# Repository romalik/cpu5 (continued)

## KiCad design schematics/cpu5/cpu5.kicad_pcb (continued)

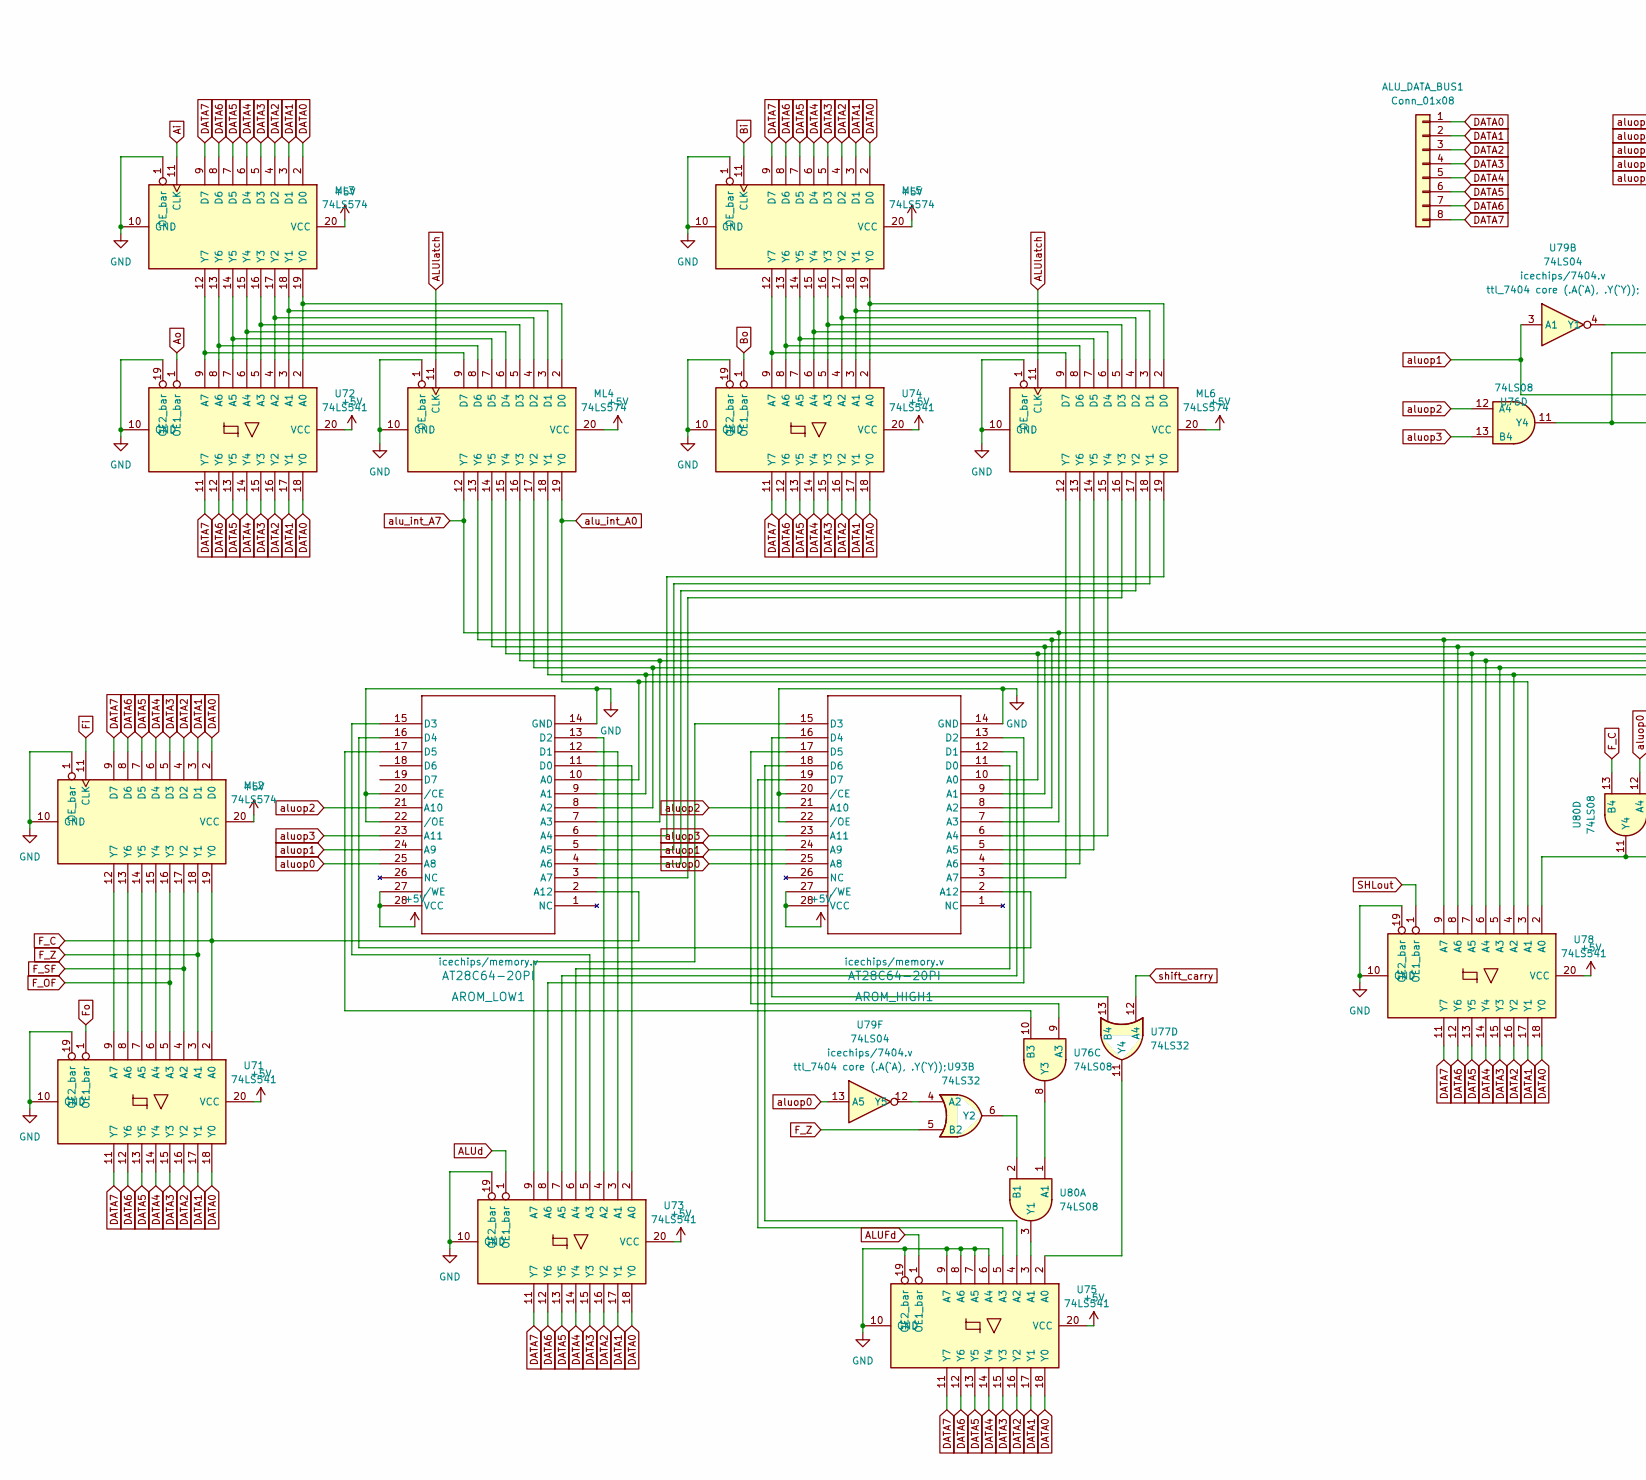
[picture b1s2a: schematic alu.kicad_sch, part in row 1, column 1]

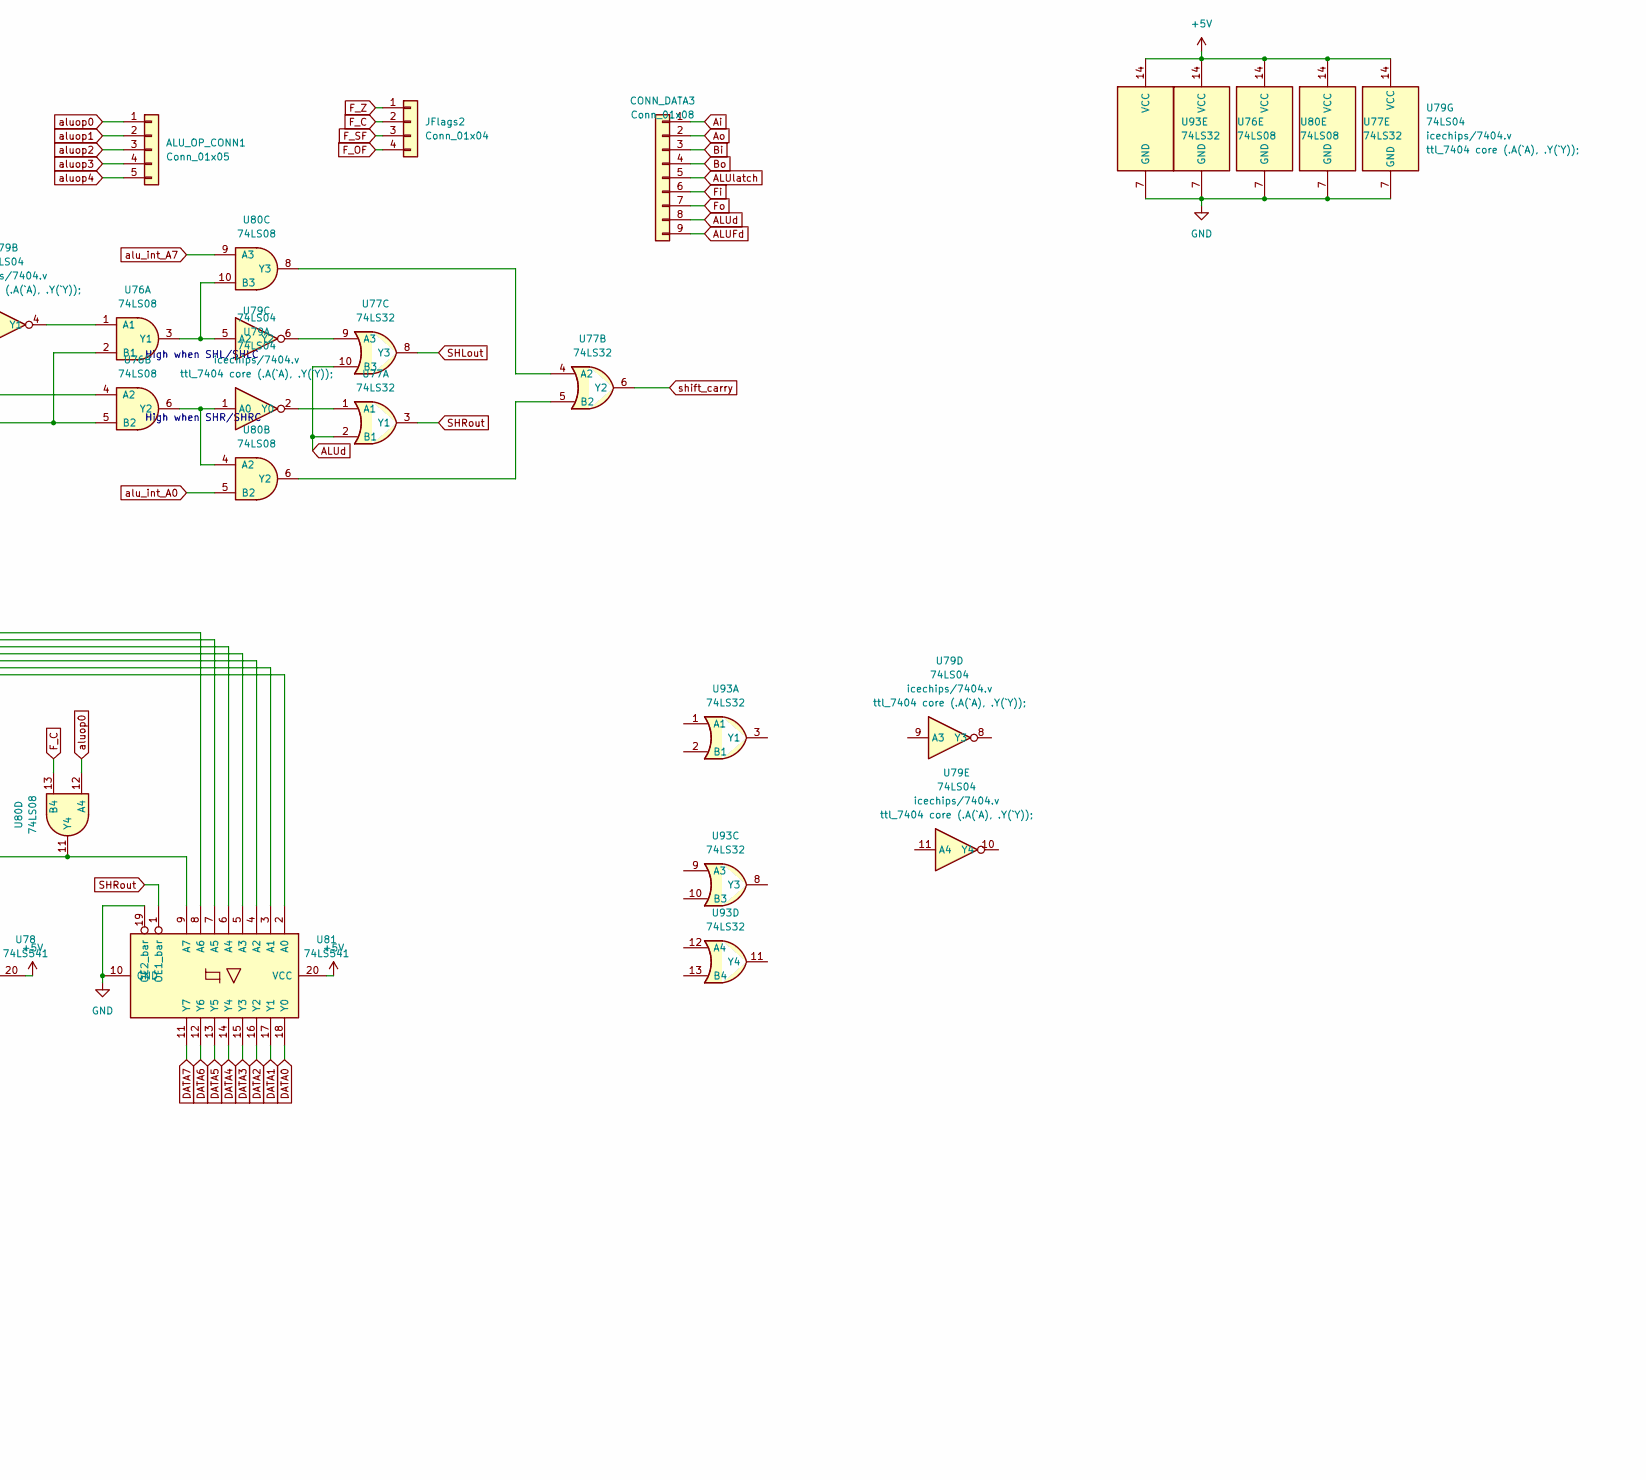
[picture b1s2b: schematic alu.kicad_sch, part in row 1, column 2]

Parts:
ALU_DATA_BUS1: Conn_01x08; PinHeader_1x08_P2.54mm_Vertical
ALU_OP_CONN1: Conn_01x05; PinHeader_1x05_P2.54mm_Vertical
AROM_HIGH1: AT28C64-20PI; DIP-28_W15.24mm
AROM_LOW1: AT28C64-20PI; DIP-28_W15.24mm
CONN_DATA3: Conn_01x08; PinHeader_1x09_P2.54mm_Vertical
JFlags2: Conn_01x04; PinHeader_1x04_P1.00mm_Vertical
ML2, ML3, ML4, ML5, ML6: 74LS574; DIP-20_W7.62mm
U71, U72, U73, U74, U75, U78, U81: 74LS541; DIP-20_W7.62mm
U76, U80: 74LS08; DIP-14_W7.62mm
U77, U93: 74LS32; DIP-14_W7.62mm
U79: 74LS04; DIP-14_W7.62mm

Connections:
+5V: AROM_HIGH1.27 (/WE), AROM_HIGH1.28 (VCC), AROM_LOW1.27 (/WE), AROM_LOW1.28 (VCC), ML2.20 (VCC), ML3.20 (VCC), ML4.20 (VCC), ML5.20 (VCC), ML6.20 (VCC), U71.20 (VCC), U72.20 (VCC), U73.20 (VCC), U74.20 (VCC), U75.20 (VCC), U76.14 (VCC), U77.14 (VCC), U78.20 (VCC), U79.14 (VCC), U80.14 (VCC), U81.20 (VCC), U93.14 (VCC); also elsewhere on the board
ALUFd: CONN_DATA3.9, U75.1 (OE1_bar); also elsewhere on the board
ALUd: CONN_DATA3.8, U73.1 (OE1_bar), U77.2 (B1), U77.10 (B3); also elsewhere on the board
ALUlatch: CONN_DATA3.5, ML4.11 (CLK), ML6.11 (CLK); also elsewhere on the board
Ai: CONN_DATA3.1, ML3.11 (CLK); also elsewhere on the board
Ao: CONN_DATA3.2, U72.1 (OE1_bar); also elsewhere on the board
Bi: CONN_DATA3.3, ML5.11 (CLK); also elsewhere on the board
Bo: CONN_DATA3.4, U74.1 (OE1_bar); also elsewhere on the board
DATA0: ALU_DATA_BUS1.1, ML2.2 (D0), ML3.2 (D0), ML5.2 (D0), U71.18 (Y0), U72.18 (Y0), U73.18 (Y0), U74.18 (Y0), U75.18 (Y0), U78.18 (Y0), U81.18 (Y0); also elsewhere on the board
DATA1: ALU_DATA_BUS1.2, ML2.3 (D1), ML3.3 (D1), ML5.3 (D1), U71.17 (Y1), U72.17 (Y1), U73.17 (Y1), U74.17 (Y1), U75.17 (Y1), U78.17 (Y1), U81.17 (Y1); also elsewhere on the board
DATA2: ALU_DATA_BUS1.3, ML2.4 (D2), ML3.4 (D2), ML5.4 (D2), U71.16 (Y2), U72.16 (Y2), U73.16 (Y2), U74.16 (Y2), U75.16 (Y2), U78.16 (Y2), U81.16 (Y2); also elsewhere on the board
DATA3: ALU_DATA_BUS1.4, ML2.5 (D3), ML3.5 (D3), ML5.5 (D3), U71.15 (Y3), U72.15 (Y3), U73.15 (Y3), U74.15 (Y3), U75.15 (Y3), U78.15 (Y3), U81.15 (Y3); also elsewhere on the board
DATA4: ALU_DATA_BUS1.5, ML2.6 (D4), ML3.6 (D4), ML5.6 (D4), U71.14 (Y4), U72.14 (Y4), U73.14 (Y4), U74.14 (Y4), U75.14 (Y4), U78.14 (Y4), U81.14 (Y4); also elsewhere on the board
DATA5: ALU_DATA_BUS1.6, ML2.7 (D5), ML3.7 (D5), ML5.7 (D5), U71.13 (Y5), U72.13 (Y5), U73.13 (Y5), U74.13 (Y5), U75.13 (Y5), U78.13 (Y5), U81.13 (Y5); also elsewhere on the board
DATA6: ALU_DATA_BUS1.7, ML2.8 (D6), ML3.8 (D6), ML5.8 (D6), U71.12 (Y6), U72.12 (Y6), U73.12 (Y6), U74.12 (Y6), U75.12 (Y6), U78.12 (Y6), U81.12 (Y6); also elsewhere on the board
DATA7: ALU_DATA_BUS1.8, ML2.9 (D7), ML3.9 (D7), ML5.9 (D7), U71.11 (Y7), U72.11 (Y7), U73.11 (Y7), U74.11 (Y7), U75.11 (Y7), U78.11 (Y7), U81.11 (Y7); also elsewhere on the board
F_C: AROM_LOW1.2 (A12), JFlags2.2, ML2.19 (Y0), U71.2 (A0), U80.13 (B4); also elsewhere on the board
F_OF: JFlags2.4, ML2.16 (Y3), U71.5 (A3); also elsewhere on the board
F_SF: JFlags2.3, ML2.17 (Y2), U71.4 (A2); also elsewhere on the board
F_Z: JFlags2.1, ML2.18 (Y1), U71.3 (A1), U93.5 (B2); also elsewhere on the board
Fi: CONN_DATA3.6, ML2.11 (CLK); also elsewhere on the board
Fo: CONN_DATA3.7, U71.1 (OE1_bar); also elsewhere on the board
GND: AROM_HIGH1.14 (GND), AROM_HIGH1.20 (/CE), AROM_HIGH1.22 (/OE), AROM_LOW1.14 (GND), AROM_LOW1.20 (/CE), AROM_LOW1.22 (/OE), ML2.1 (OE_bar), ML2.10 (GND), ML3.1 (OE_bar), ML3.10 (GND), ML4.1 (OE_bar), ML4.10 (GND), ML5.1 (OE_bar), ML5.10 (GND), ML6.1 (OE_bar), ML6.10 (GND), U71.10 (GND), U71.19 (OE2_bar), U72.10 (GND), U72.19 (OE2_bar), U73.10 (GND), U73.19 (OE2_bar), U74.10 (GND), U74.19 (OE2_bar), U75.6 (A4), U75.7 (A5), U75.8 (A6), U75.9 (A7), U75.10 (GND), U75.19 (OE2_bar), U76.7 (GND), U77.7 (GND), U78.10 (GND), U78.19 (OE2_bar), U79.7 (GND), U80.7 (GND), U81.10 (GND), U81.19 (OE2_bar), U93.7 (GND); also elsewhere on the board
IR0: ALU_OP_CONN1.1, AROM_HIGH1.25 (A8), AROM_LOW1.25 (A8), U79.13 (A5), U80.12 (A4); also elsewhere on the board
IR1: ALU_OP_CONN1.2, AROM_HIGH1.24 (A9), AROM_LOW1.24 (A9), U76.4 (A2), U79.3 (A1); also elsewhere on the board
IR2: ALU_OP_CONN1.3, AROM_HIGH1.21 (A10), AROM_LOW1.21 (A10), U76.12 (A4); also elsewhere on the board
IR3: ALU_OP_CONN1.4, AROM_HIGH1.23 (A11), AROM_LOW1.23 (A11), U76.13 (B4); also elsewhere on the board
IR4: ALU_OP_CONN1.5; also elsewhere on the board
unnamed: AROM_HIGH1.2 (A12), AROM_LOW1.16 (D4)
unnamed: AROM_HIGH1.3 (A7), ML6.12 (Y7)
unnamed: AROM_HIGH1.4 (A6), ML6.13 (Y6)
unnamed: AROM_HIGH1.5 (A5), ML6.14 (Y5)
unnamed: AROM_HIGH1.6 (A4), ML6.15 (Y4)
unnamed: AROM_HIGH1.8 (A2), ML4.13 (Y6), U78.9 (A7), U81.7 (A5)
unnamed: AROM_HIGH1.9 (A1), ML4.14 (Y5), U78.8 (A6), U81.6 (A4)
unnamed: AROM_HIGH1.10 (A0), ML4.15 (Y4), U78.7 (A5), U81.5 (A3)
unnamed: AROM_HIGH1.11 (D0), U73.6 (A4)
unnamed: AROM_HIGH1.12 (D1), U73.7 (A5)
unnamed: AROM_HIGH1.13 (D2), U73.8 (A6)
unnamed: AROM_HIGH1.15 (D3), U73.9 (A7)
unnamed: AROM_HIGH1.16 (D4), U77.13 (B4)
unnamed: AROM_HIGH1.17 (D5), U76.9 (A3)
unnamed: AROM_HIGH1.18 (D6), U75.4 (A2)
unnamed: AROM_HIGH1.19 (D7), U75.5 (A3)
unnamed: AROM_LOW1.3 (A7), ML6.16 (Y3)
unnamed: AROM_LOW1.4 (A6), ML6.17 (Y2)
unnamed: AROM_LOW1.5 (A5), ML6.18 (Y1)
unnamed: AROM_LOW1.6 (A4), ML6.19 (Y0)
unnamed: AROM_LOW1.7 (A3), ML4.16 (Y3), U78.6 (A4), U81.4 (A2)
unnamed: AROM_LOW1.8 (A2), ML4.17 (Y2), U78.5 (A3), U81.3 (A1)
unnamed: AROM_LOW1.9 (A1), ML4.18 (Y1), U78.4 (A2), U81.2 (A0)
unnamed: AROM_LOW1.11 (D0), U73.2 (A0)
unnamed: AROM_LOW1.12 (D1), U73.3 (A1)
unnamed: AROM_LOW1.13 (D2), U73.4 (A2)
unnamed: AROM_LOW1.15 (D3), U73.5 (A3)
unnamed: AROM_LOW1.17 (D5), U76.10 (B3)
unnamed: ML2.12 (Y7), U71.9 (A7)
unnamed: ML2.13 (Y6), U71.8 (A6)
unnamed: ML2.14 (Y5), U71.7 (A5)
unnamed: ML2.15 (Y4), U71.6 (A4)
unnamed: ML3.12 (Y7), ML4.9 (D7), U72.9 (A7)
unnamed: ML3.13 (Y6), ML4.8 (D6), U72.8 (A6)
unnamed: ML3.14 (Y5), ML4.7 (D5), U72.7 (A5)
unnamed: ML3.15 (Y4), ML4.6 (D4), U72.6 (A4)
unnamed: ML3.16 (Y3), ML4.5 (D3), U72.5 (A3)
unnamed: ML3.17 (Y2), ML4.4 (D2), U72.4 (A2)
unnamed: ML3.18 (Y1), ML4.3 (D1), U72.3 (A1)
unnamed: ML3.19 (Y0), ML4.2 (D0), U72.2 (A0)
unnamed: ML5.12 (Y7), ML6.9 (D7), U74.9 (A7)
unnamed: ML5.13 (Y6), ML6.8 (D6), U74.8 (A6)
unnamed: ML5.14 (Y5), ML6.7 (D5), U74.7 (A5)
unnamed: ML5.15 (Y4), ML6.6 (D4), U74.6 (A4)
unnamed: ML5.16 (Y3), ML6.5 (D3), U74.5 (A3)
unnamed: ML5.17 (Y2), ML6.4 (D2), U74.4 (A2)
unnamed: ML5.18 (Y1), ML6.3 (D1), U74.3 (A1)
unnamed: ML5.19 (Y0), ML6.2 (D0), U74.2 (A0)
unnamed: U75.2 (A0), U77.11 (Y4)
unnamed: U75.3 (A1), U80.3 (Y1)
unnamed: U76.1 (A1), U79.4 (Y1)
unnamed: U76.3 (Y1), U79.5 (A2), U80.10 (B3)
unnamed: U76.6 (Y2), U79.1 (A0), U80.4 (A2)
unnamed: U76.8 (Y3), U80.1 (A1)
unnamed: U76.2 (B1), U76.5 (B2), U76.11 (Y4)
unnamed: U77.1 (A1), U79.2 (Y0)
unnamed: U77.4 (A2), U80.8 (Y3)
unnamed: U77.5 (B2), U80.6 (Y2)
unnamed: U77.9 (A3), U79.6 (Y2)
unnamed: U78.2 (A0), U80.11 (Y4), U81.9 (A7)
unnamed: U79.12 (Y5), U93.4 (A2)
unnamed: U80.2 (B1), U93.6 (Y2)
SHLout: U77.8 (Y3), U78.1 (OE1_bar)
SHRout: U77.3 (Y1), U81.1 (OE1_bar)
alu_int_A0: AROM_LOW1.10 (A0), ML4.19 (Y0), U78.3 (A1), U80.5 (B2)
alu_int_A7: AROM_HIGH1.7 (A3), ML4.12 (Y7), U80.9 (A3), U81.8 (A6)
shift_carry: U77.6 (Y2), U77.12 (A4)

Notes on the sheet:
High when SHR/SHRC
High when SHL/SHLC

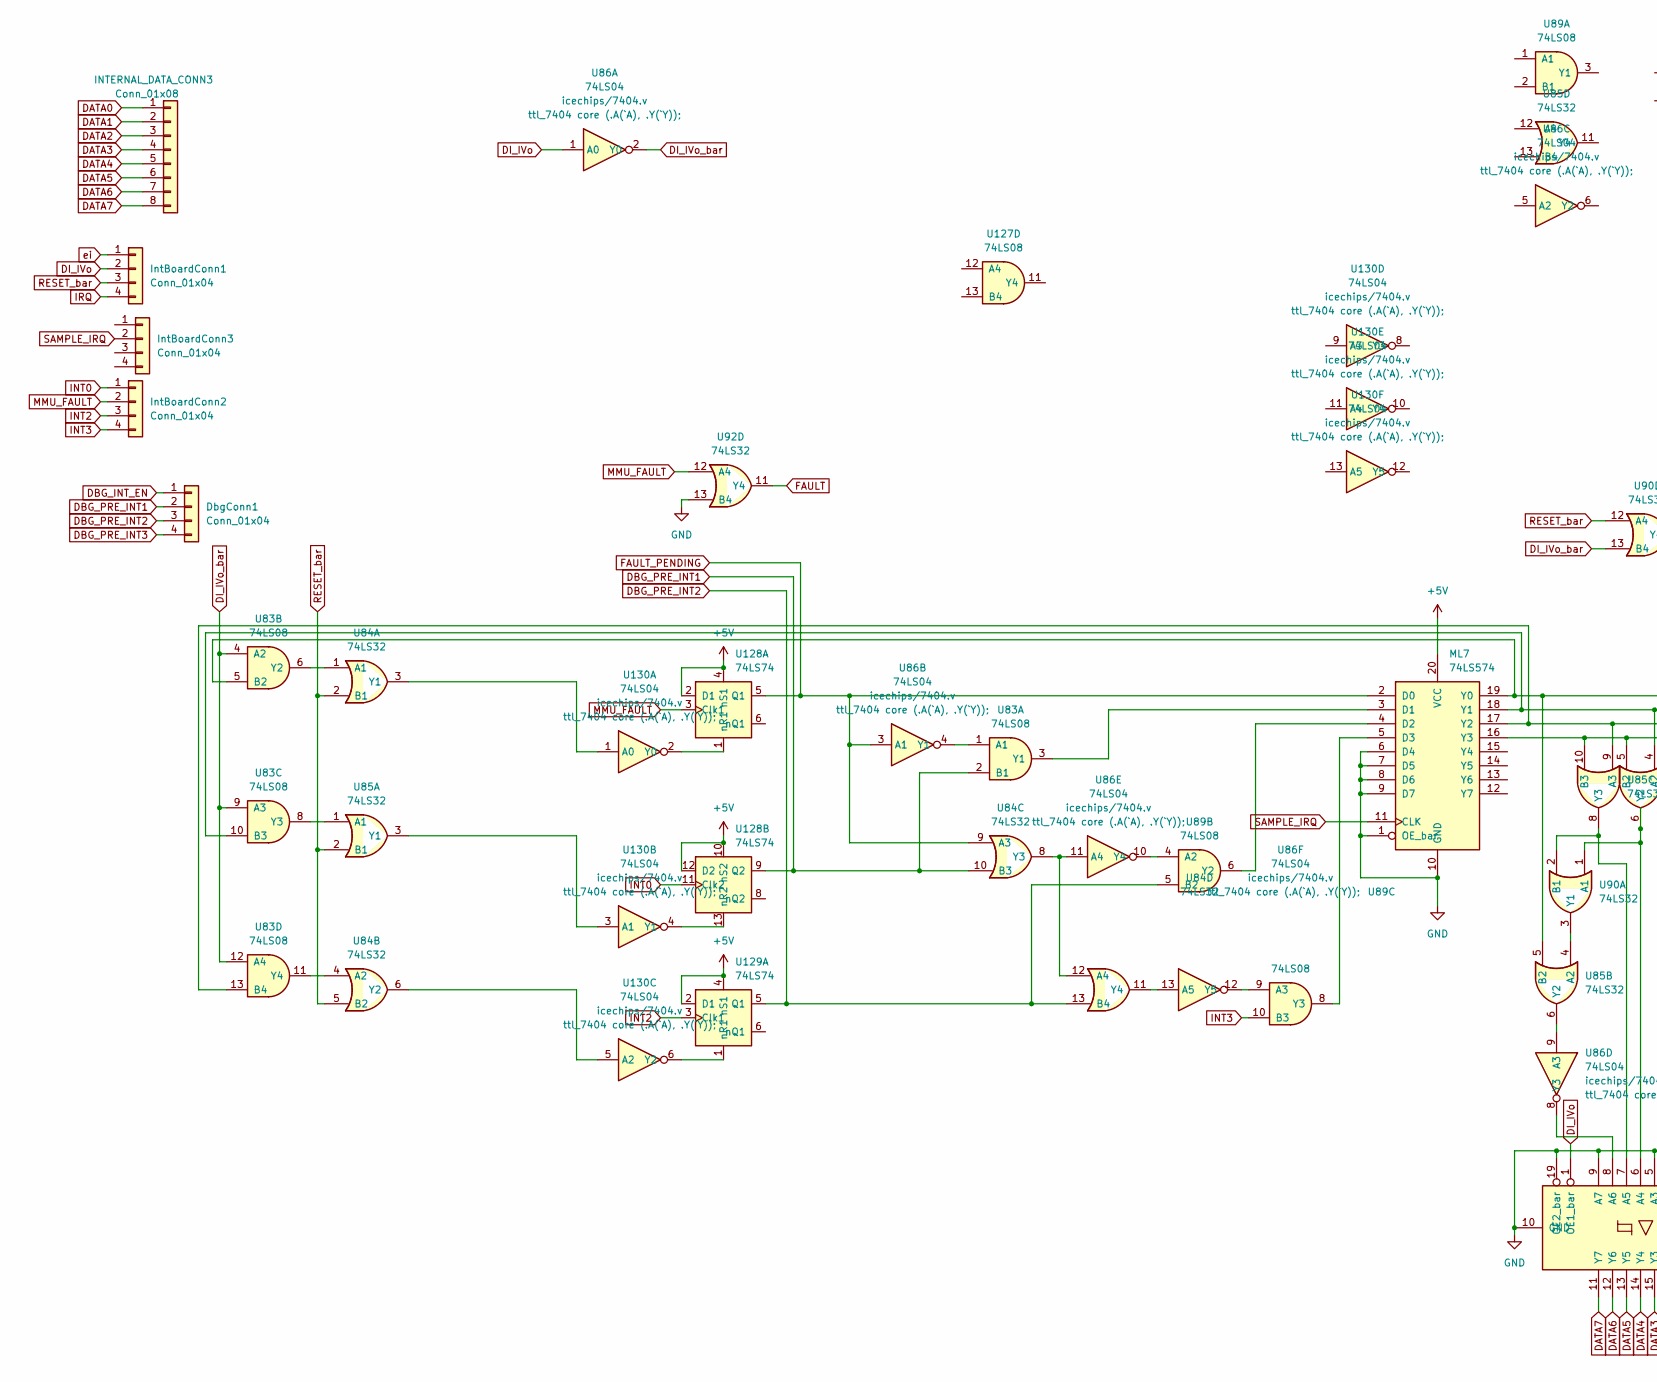
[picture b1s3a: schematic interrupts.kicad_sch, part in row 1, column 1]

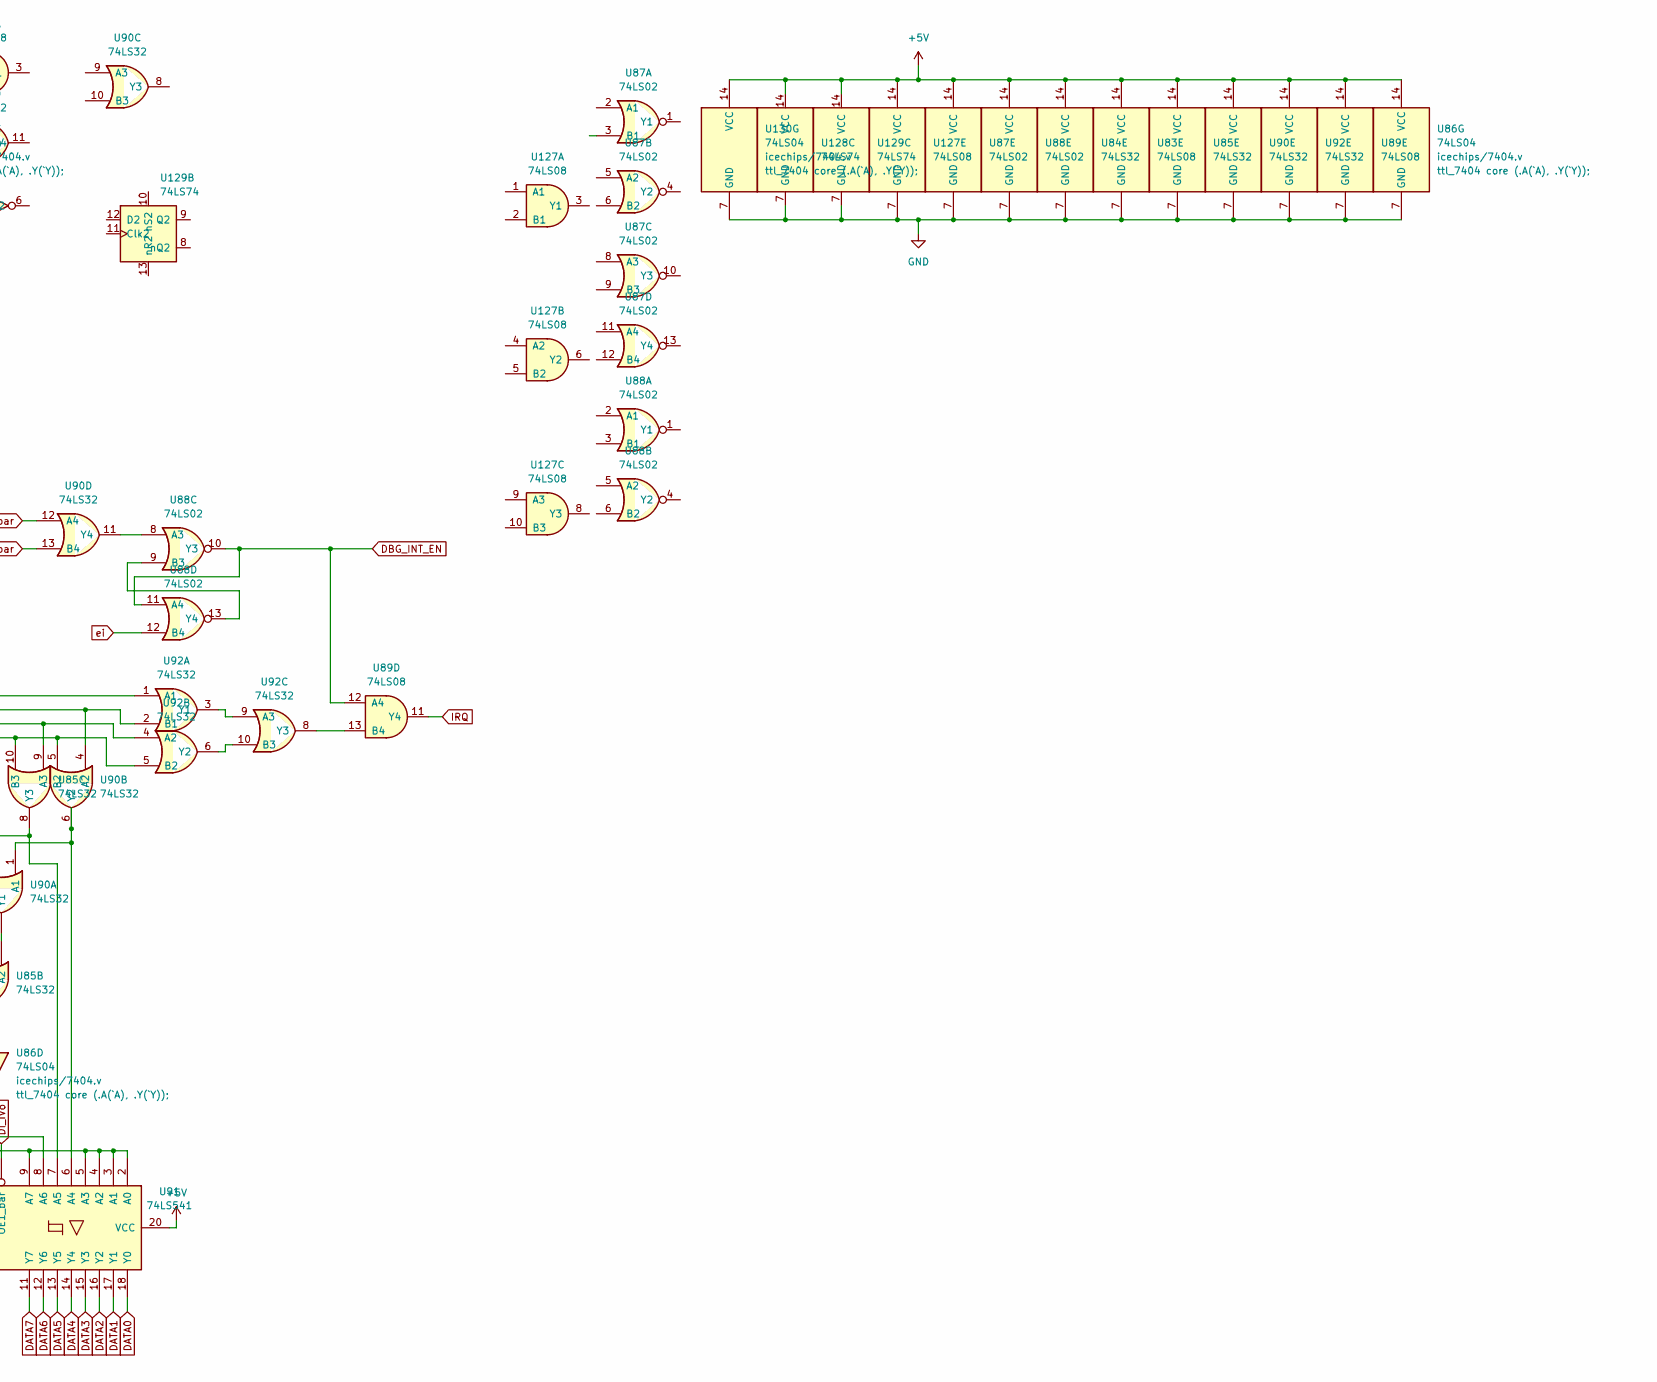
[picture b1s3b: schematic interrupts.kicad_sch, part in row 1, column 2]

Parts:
DbgConn1: Conn_01x04; PinHeader_1x04_P1.00mm_Vertical
INTERNAL_DATA_CONN3: Conn_01x08; PinHeader_1x08_P2.54mm_Vertical
IntBoardConn1, IntBoardConn2, IntBoardConn3: Conn_01x04; PinHeader_1x04_P1.00mm_Vertical
ML7: 74LS574; DIP-20_W7.62mm
U83, U89, U127: 74LS08; DIP-14_W7.62mm
U84, U85, U90, U92: 74LS32; DIP-14_W7.62mm
U86, U130: 74LS04; DIP-14_W7.62mm
U87, U88: 74LS02; DIP-14_W7.62mm
U91: 74LS541; DIP-20_W7.62mm
U128, U129: 74LS74; DIP-14_W7.62mm

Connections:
+5V: ML7.20 (VCC), U83.14 (VCC), U84.14 (VCC), U85.14 (VCC), U86.14 (VCC), U87.14 (VCC), U88.14 (VCC), U89.14 (VCC), U90.14 (VCC), U91.20 (VCC), U92.14 (VCC), U127.14 (VCC), U128.2 (D1), U128.4 (nS1), U128.10 (nS2), U128.12 (D2), U128.14 (VCC), U129.2 (D1), U129.4 (nS1), U129.14 (VCC), U130.14 (VCC); also elsewhere on the board
DATA0: INTERNAL_DATA_CONN3.1, U91.18 (Y0); also elsewhere on the board
DATA1: INTERNAL_DATA_CONN3.2, U91.17 (Y1); also elsewhere on the board
DATA2: INTERNAL_DATA_CONN3.3, U91.16 (Y2); also elsewhere on the board
DATA3: INTERNAL_DATA_CONN3.4, U91.15 (Y3); also elsewhere on the board
DATA4: INTERNAL_DATA_CONN3.5, U91.14 (Y4); also elsewhere on the board
DATA5: INTERNAL_DATA_CONN3.6, U91.13 (Y5); also elsewhere on the board
DATA6: INTERNAL_DATA_CONN3.7, U91.12 (Y6); also elsewhere on the board
DATA7: INTERNAL_DATA_CONN3.8, U91.11 (Y7); also elsewhere on the board
DBG_INT_EN: DbgConn1.1, U88.10 (Y3), U88.11 (A4), U89.12 (A4); also elsewhere on the board
DBG_PRE_INT1: DbgConn1.2, U83.2 (B1), U84.10 (B3), U128.9 (Q2); also elsewhere on the board
DBG_PRE_INT2: DbgConn1.3, U84.13 (B4), U89.5 (B2), U129.5 (Q1); also elsewhere on the board
DBG_PRE_INT3: DbgConn1.4; also elsewhere on the board
DI_IVo: IntBoardConn1.2, U86.1 (A0), U91.1 (OE1_bar); also elsewhere on the board
DI_IVo_bar: U83.4 (A2), U83.9 (A3), U83.12 (A4), U86.2 (Y0), U90.13 (B4)
FAULT: U92.11 (Y4); also elsewhere on the board
FAULT_PENDING: ML7.2 (D0), U84.9 (A3), U86.3 (A1), U128.5 (Q1); also elsewhere on the board
GND: ML7.1 (OE_bar), ML7.6 (D4), ML7.7 (D5), ML7.8 (D6), ML7.9 (D7), ML7.10 (GND), U83.7 (GND), U84.7 (GND), U85.7 (GND), U86.7 (GND), U87.7 (GND), U88.7 (GND), U89.7 (GND), U90.7 (GND), U91.2 (A0), U91.3 (A1), U91.4 (A2), U91.5 (A3), U91.9 (A7), U91.10 (GND), U91.19 (OE2_bar), U92.7 (GND), U92.13 (B4), U127.7 (GND), U128.7 (GND), U129.7 (GND), U130.7 (GND); also elsewhere on the board
INT0: IntBoardConn2.1, U128.11 (Clk2)
INT2: IntBoardConn2.3, U129.3 (Clk1)
INT3: IntBoardConn2.4, U89.10 (B3)
IRQ: IntBoardConn1.4, U89.11 (Y4); also elsewhere on the board
MMU_FAULT: IntBoardConn2.2, U92.12 (A4), U128.3 (Clk1); also elsewhere on the board
unnamed: ML7.3 (D1), U83.3 (Y1)
unnamed: ML7.4 (D2), U89.6 (Y2)
unnamed: ML7.5 (D3), U89.8 (Y3)
unnamed: ML7.16 (Y3), U85.10 (B3), U90.5 (B2), U92.5 (B2)
unnamed: ML7.17 (Y2), U83.13 (B4), U85.9 (A3), U92.4 (A2)
unnamed: ML7.18 (Y1), U83.10 (B3), U90.4 (A2), U92.2 (B1)
unnamed: ML7.19 (Y0), U83.5 (B2), U85.5 (B2), U92.1 (A1)
unnamed: U83.1 (A1), U86.4 (Y1)
unnamed: U83.6 (Y2), U84.1 (A1)
unnamed: U83.8 (Y3), U85.1 (A1)
unnamed: U83.11 (Y4), U84.4 (A2)
unnamed: U84.11 (Y4), U86.13 (A5)
unnamed: U84.8 (Y3), U84.12 (A4), U86.11 (A4)
unnamed: U85.4 (A2), U90.3 (Y1)
unnamed: U85.6 (Y2), U86.9 (A3)
unnamed: U85.8 (Y3), U90.2 (B1), U91.7 (A5)
unnamed: U86.8 (Y3), U91.8 (A6)
unnamed: U86.10 (Y4), U89.4 (A2)
unnamed: U86.12 (Y5), U89.9 (A3)
unnamed: U88.8 (A3), U90.11 (Y4)
unnamed: U88.9 (B3), U88.13 (Y4)
unnamed: U89.13 (B4), U92.8 (Y3)
unnamed: U90.1 (A1), U90.6 (Y2), U91.6 (A4)
unnamed: U92.3 (Y1), U92.9 (A3)
unnamed: U92.6 (Y2), U92.10 (B3)
unnamed: U128.1 (nR1), U130.2 (Y0)
unnamed: U128.13 (nR2), U130.4 (Y1)
unnamed: U129.1 (nR1), U130.6 (Y2)
unnamed: U84.3 (Y1), U130.1 (A0)
unnamed: U85.3 (Y1), U130.3 (A1)
unnamed: U84.6 (Y2), U130.5 (A2)
RESET_bar: IntBoardConn1.3, U84.2 (B1), U84.5 (B2), U85.2 (B1), U90.12 (A4); also elsewhere on the board
SAMPLE_IRQ: IntBoardConn3.2, ML7.11 (CLK); also elsewhere on the board
ei: IntBoardConn1.1, U88.12 (B4); also elsewhere on the board
